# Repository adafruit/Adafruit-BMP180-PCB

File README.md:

# PCB for the Adafruit 5V ready BMP180 Barometric 

This is the PCB for the Adafruit 5V ready BMP180 Barometric 
Pressure/Temperature/Altitude Sensor (BMP085 upgrade)

Format is EagleCAD schematic and board layout

This precision sensor from Bosch is the best low-cost sensing solution for measuring barometric pressure and temperature. Because pressure changes with altitude you can also use it as an altimeter! The sensor is soldered onto a PCB with a 3.3V regulator, I2C level shifter and pull-up resistors on the I2C pins.

The BMP180 is the next-generation of sensors from Bosch, and replaces the BMP085. The good news is that it is completely identical to the BMP085 in terms of firmware/software - you can use our BMP085 tutorial and any example code/libraries as a drop-in replacement. The XCLR pin is not physically present on the BMP180 so if you need to know that data is ready you will need to query the I2C bus.

This board is 5V compliant - a 3.3V regulator and a i2c level shifter circuit is included so you can use this sensor safely with 5V logic and power.

Using the sensor is easy. For example, if you're using an Arduino, simply connect the VIN pin to the 5V voltage pin, GND to ground, SCL to I2C Clock (Analog 5) and SDA to I2C Data (Analog 4). Then download our BMP085/BMP180 Arduino library and example code for temperature, pressure and altitude calculation. Install the library, and load the example sketch. Immediately you'll have precision temperature, pressure and altitude data.

[Our detailed tutorial has all the info you need including links to software and installation instructions. It includes more information about the BMP180 so you can understand the sensor in depth](http://learn.adafruit.com/bmp085) including how to properly calculate altitude based on sea-level barometric pressure.

## License

Adafruit invests time and resources providing this open source design, 
please support Adafruit and open-source hardware by purchasing 
products from Adafruit!

Designed by Adafruit Industries.  
Creative Commons Attribution, Share-Alike license, check license.txt for more information
All text above must be included in any redistribution

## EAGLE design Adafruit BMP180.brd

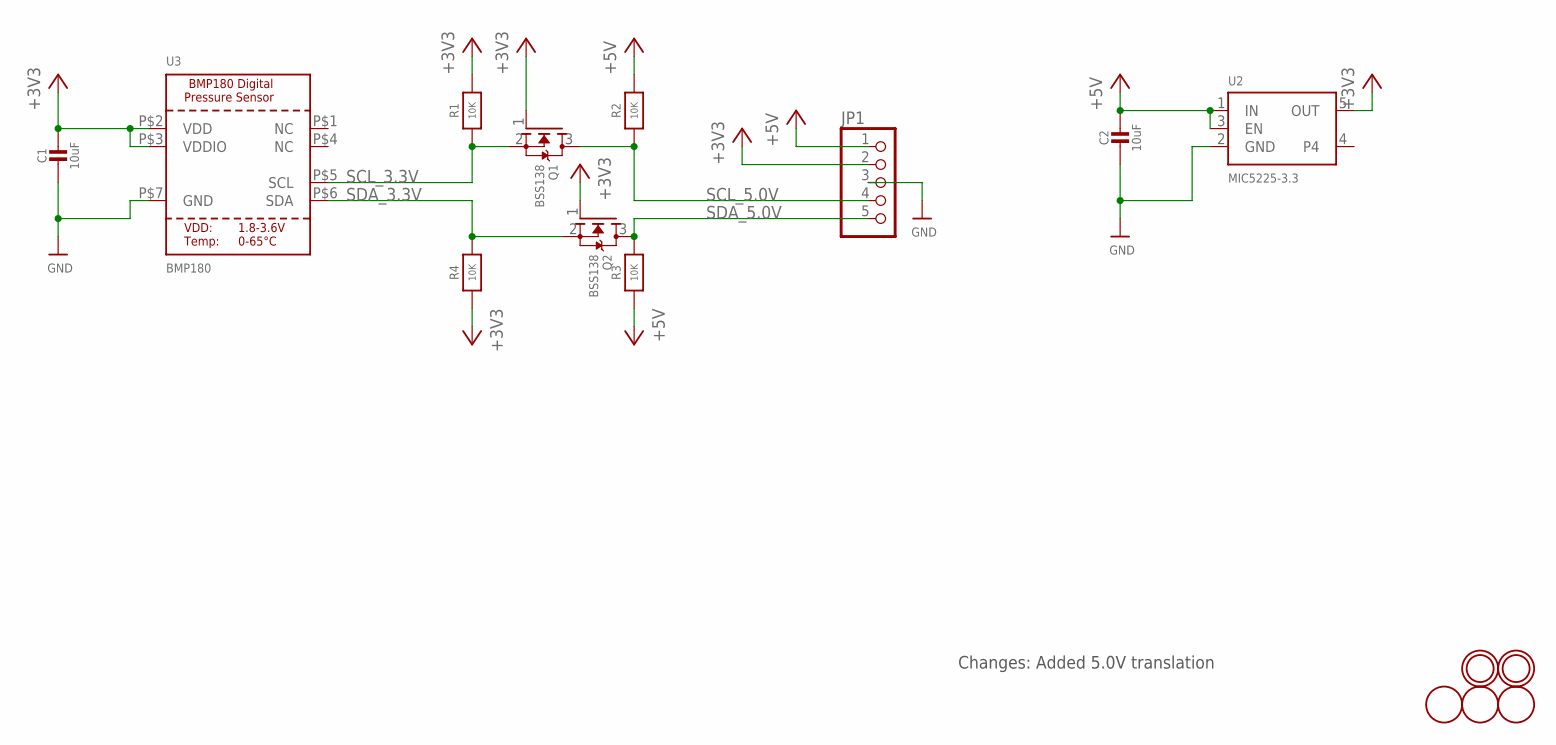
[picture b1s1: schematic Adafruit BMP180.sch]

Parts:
C1, C2: 10uF; 0805-NO
JP1: HEADER-1X570MIL; 1X05_ROUND_70
Q1, Q2: BSS138; SOT23
R1, R3, R4: 10K; 0805-NO
R2: 10K; _0805MP
U2: MIC5225-3.3; SOT23-5
U3: BMP180; BMP180_EXTENDED
U$1, U$5, U$15: FIDUCIAL; FIDUCIAL_1MM
U$7, U$8: MOUNTINGHOLE2.0; MOUNTINGHOLE_2.0_PLATED

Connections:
+3V3: C1.1, JP1.2, Q1.1 (G), Q2.1 (G), R1.2, R4.1, U2.5 (OUT), U3.P$2 (VDD), U3.P$3 (VDDIO)
+5V: C2.1, JP1.1, R2.2, R3.1, U2.1 (IN), U2.3 (EN)
GND: C1.2, C2.2, JP1.3, U2.2 (GND), U3.P$7 (GND)
SCL_3.3V: Q1.2 (S), R1.1, U3.P$5 (SCL)
SCL_5.0V: JP1.4, Q1.3 (D), R2.1
SDA_3.3V: Q2.2 (S), R4.2, U3.P$6 (SDA)
SDA_5.0V: JP1.5, Q2.3 (D), R3.2

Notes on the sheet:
Changes: Added 5.0V translation

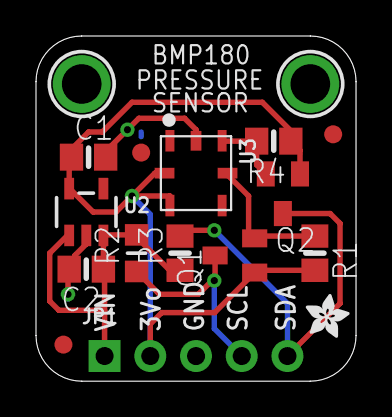
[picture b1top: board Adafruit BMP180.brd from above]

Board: 2 copper layers, 17.8 x 19.2 mm, 18 parts (1 on the bottom side), 7 nets.

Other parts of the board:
U$2, U$6: ADAFRUIT_2.5MM

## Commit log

2014-05-16 w00p
2019-05-07 readme + image
